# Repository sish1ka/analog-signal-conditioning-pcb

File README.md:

# Analog Signal-Conditioning PCB

## Overview

This project involves the design of a small analog signal-conditioning circuit intended to convert a 0–1 V sensor signal into a 0–3 V output suitable for microcontroller ADC interfacing.

The circuit was designed and simulated using LTspice and implemented
as a 2-layer PCB using KiCad.

## Objectives

- Design an analog amplification stage
- Implement low-pass filtering
- Maintain an ADC-compatible 0–3 V output
- Verify circuit behavior through simulation
- Design and verify a 2-layer PCB

## Tools

- LTspice
- KiCad

## Circuit Design

## Design Summary

| Parameter | Value |
|---|---:|
| Input signal | 0–1 V |
| Output signal | 0–3 V |
| Supply | +5 V |
| Amplifier | LM358 non-inverting |
| Voltage gain | 3× |
| Low-pass filter | 1st-order RC |
| Filter cutoff | ~1.59 kHz |
| PCB layers | 2 |
| PCB dimensions | 60 × 40 mm |

## LTspice Simulation

### Frequency Response

### Transient Response

### Verification Procedure

The circuit was verified using a node-by-node transient analysis.
Each verification step checks a specific electrical condition before
proceeding to the next stage.

### 1. Op-Amp Supply Voltage Verification

**Purpose:**  
Verify that the op-amp is receiving the required +5 V supply voltage before evaluating signal behavior.

**Procedure:**

1. Run a transient analysis in LTspice.
2. Probe the op-amp positive supply node (`V+`).
3. Confirm that the supply voltage is approximately +5 V.
4. Verify that the supply voltage remains stable throughout the simulation.

**Expected Result:**

| Parameter | Expected |
|---|---:|
| Supply voltage (`V+`) | +5 V |
| Supply stability | Stable |

**Measured Result:**  
`V+ = 5.00 V`

**Result:** Pass

### 2. Voltage Gain Verification

**Purpose:**  
Verify that the measured voltage gain agrees with the theoretical gain determined by the feedback resistors.

**Theoretical Gain:**

$$
A_v = 1 + \frac{R_2}{R_1}
$$

$$
A_v = 1 + \frac{20k\Omega}{10k\Omega} = 3
$$

**Procedure:**
1. Measure the input signal amplitude from the transient analysis.
2. Measure the output signal amplitude.
3. Calculate the measured voltage gain using:

$$
A_v = \frac{V_{out}}{V_{in}}
$$

4. Compare the measured gain with the theoretical gain of 3×.

**Expected Result:**

| Parameter | Expected |
|---|---:|
| Theoretical gain | 3× |
| Measured gain | ~3× |
| Gain error | Minimal |

**Measured Result:**  
`Theoretical gain = 3.00×`  
`Measured gain = Vout / Vin = 3.00×`

**Result:** Pass

### 3. Input and Op-Amp Output Verification

**Purpose:**  
Verify that the input signal has the expected amplitude and frequency, and that the op-amp produces the expected amplified output.

**Procedure:**
1. Run a transient analysis for 100 ms in LTspice.
2. Probe the input node of the op-amp.
3. Verify that the input signal is a 50 mV amplitude, 60 Hz sine wave centered around 0 V.
4. Probe the op-amp output node.
5. Verify that the output waveform follows the input waveform with the expected 3× voltage gain.
6. Compare the measured input and output amplitudes.

**Expected Result:**

| Parameter | Input | Op-Amp Output |
|---|---:|---:|
| Peak amplitude | 50 mV | ~150 mV |
| Peak-to-peak voltage | 100 mV | ~300 mV |
| Frequency | 60 Hz | 60 Hz |
| DC offset | 0 V | 0 V |
| Voltage gain | — | ~3× |

**Measured Result:**  
`Vin = 50 mV peak`  
`Vout = 150 mV peak`  
`f = 60 Hz`  
`Gain = Vout / Vin ≈ 3`

**Result:**  Pass

### 4. Filter Response Verification

**Purpose:**  
Verify the frequency response of the RC low-pass filter and confirm that the measured cutoff frequency agrees with the theoretical value.

**Filter Configuration:**

| Component | Value |
|---|---:|
| R3 | 10 kΩ |
| C1 | 10 nF |
| Filter type | Low-pass |

**Theoretical Cutoff Frequency:**

$$
f_c = \frac{1}{2\pi R_3 C_1}
$$

$$
f_c = \frac{1}{2\pi(10\,k\Omega)(10\,nF)}
$$

$$
f_c \approx 1.59\,kHz
$$

**Procedure:**
1. Set the input voltage source AC amplitude to 1 V for AC analysis.
2. Run an AC analysis using:
   `.ac dec 100 10 100k`
3. Plot the output voltage magnitude `V(VOUT)`.
4. Identify the low-frequency output magnitude.
5. Determine the frequency where the magnitude is approximately 3 dB below the low-frequency value.
6. Compare the measured cutoff frequency with the theoretical value.

**Expected Result:**

| Parameter | Expected |
|---|---:|
| Low-frequency gain | ~9.54 dB |
| Filter type | Low-pass |
| Theoretical cutoff frequency | ~1.59 kHz |
| Magnitude at cutoff | ~6.54 dB |
| Roll-off after cutoff | ~−20 dB/decade |

The low-frequency gain is approximately 9.54 dB because the op-amp provides a voltage gain of 3×:

$$
20\log_{10}(3) \approx 9.54\ dB
$$

Therefore, the -3 dB cutoff point is approximately:

$$
9.54 - 3 = 6.54\ dB
$$

**Measured Result:**  
`Low-frequency gain ≈ 9.5 dB`  
`Measured cutoff frequency ≈ 1.6 kHz`

The measured cutoff frequency agrees closely with the theoretical value of approximately 1.59 kHz.

**Result:** Pass

### Results

| Verification | Theoretical | Measured | Error | Result |
|---|---:|---:|---:|---|
| Voltage gain | 3.00× | 3.00× | 0% | Pass |
| Low-frequency gain | 9.54 dB | 9.5 dB | 0.42% | Pass |
| Filter cutoff | 1.59 kHz | 1.60 kHz | 0.63% | Pass |
| PCB DRC errors | 0 | 0 | — | Pass |

## PCB Design

### Components

| Reference | Component | Value | Footprint |
|---|---|---|---|
| U1 | LM358 Dual Op-Amp | LM358 | `Package_SO:SOIC-8_3.9x4.9mm_P1.27mm` |
| R1 | Resistor | 10 kΩ | `Resistor_SMD:R_0805_2012Metric_Pad1.18x1.45mm_HandSolder` |
| R2 | Resistor | 20 kΩ | `Resistor_SMD:R_0805_2012Metric_Pad1.18x1.45mm_HandSolder` |
| R3 | Resistor | 10 kΩ | `Resistor_SMD:R_0805_2012Metric_Pad1.18x1.45mm_HandSolder` |
| C1 | Ceramic Capacitor | 10 nF | `Capacitor_SMD:C_0805_2012Metric_Pad1.18x1.45mm_HandSolder` |
| C2 | Ceramic Capacitor | 100 nF | `Capacitor_SMD:C_0805_2012Metric_Pad1.18x1.45mm_HandSolder` |
| J1 | 2-Pin Terminal Block | Input | `TerminalBlock_Altech:Altech_AK100_1x02_P5.00mm` |
| J2 | 2-Pin Terminal Block | Output | `TerminalBlock_Altech:Altech_AK100_1x02_P5.00mm` |
| J3 | 2-Pin Terminal Block | Power | `TerminalBlock_Altech:Altech_AK100_1x02_P5.00mm` |

### Connector Pinout

| Connector | Pin 1 | Pin 2 |
|---|---|---|
| J1 – Input | VIN | GND |
| J2 – Output | VOUT | GND |
| J3 – Power | +5 V | GND |

### Circuit Parameters

| Parameter | Value |
|---|---:|
| Supply Voltage | +5 V |
| Input Range | 0–1 V |
| Voltage Gain | 3× |
| Output Range | 0–3 V |
| Filter | RC Low-Pass |
| Cutoff Frequency | ~1.59 kHz |

### KiCAD schematic 

### PCB Layout

### 3D View

### Fabrication Outputs

Gerber and drill files were generated using KiCad for PCB manufacturing.

The fabrication outputs include:
- Front and back copper
- Front and back solder mask
- Silkscreen
- Board outline
- Drill files

The generated files are available in `KiCad/Gerbers/`.

### PCB Design Verification

The PCB layout was checked using KiCad's Design Rules Checker (DRC).

**Result:**
- DRC errors: 0
- Unconnected items: 0
- Board outline: 60 × 40 mm

The design passed the final DRC check before fabrication outputs were generated.

## Files

- `Documentation/` — design images and results
- `KiCad/` — schematic and PCB design files
- `LTspice/` — circuit simulations
- `BOM/` — bill of materials
- `Gerbers/` — manufacturing outputs

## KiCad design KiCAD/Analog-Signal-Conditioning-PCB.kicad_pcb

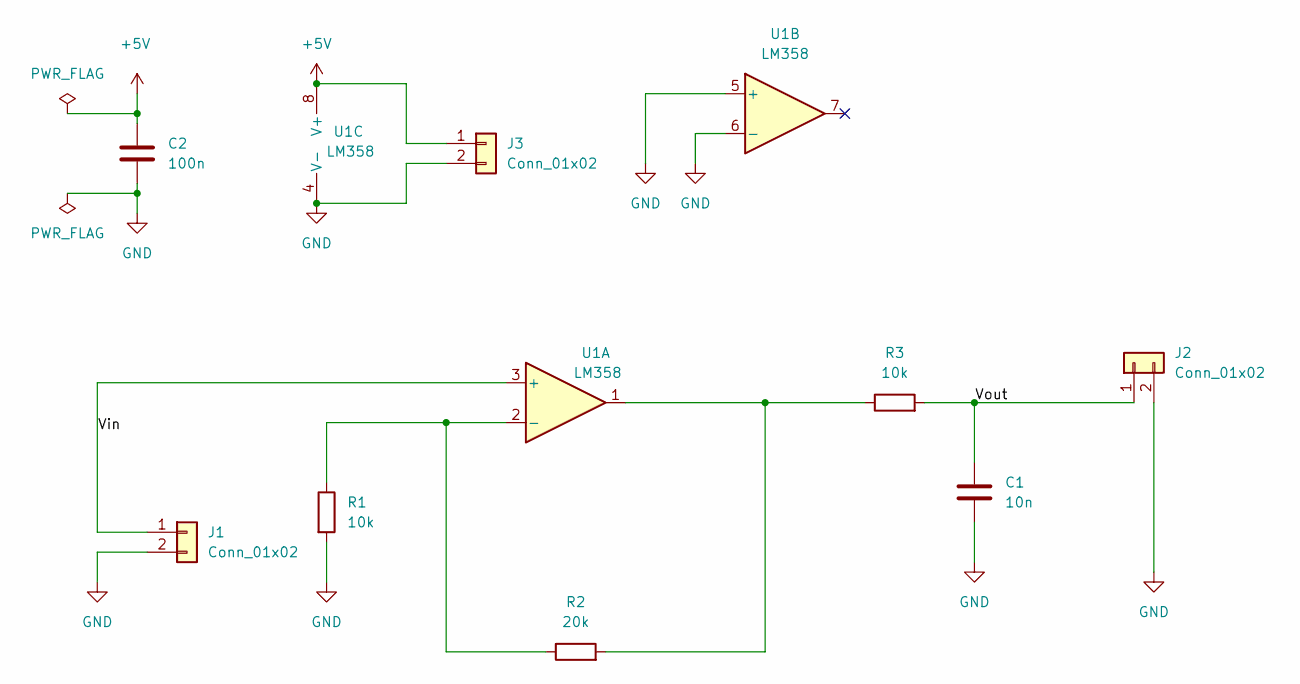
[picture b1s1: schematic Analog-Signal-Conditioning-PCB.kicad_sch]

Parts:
C1: 10n; C_0805_2012Metric_Pad1.18x1.45mm_HandSolder
C2: 100n; C_0805_2012Metric_Pad1.18x1.45mm_HandSolder
J1, J2, J3: Conn_01x02; Altech_AK100_1x02_P5.00mm
R1, R3: 10k; R_0805_2012Metric_Pad1.20x1.40mm_HandSolder
R2: 20k; R_0805_2012Metric_Pad1.20x1.40mm_HandSolder
U1: LM358; SOIC-8_3.9x4.9mm_P1.27mm

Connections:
+5V: C2.1, J3.1, U1.8 (V+)
/Vin: J1.1, U1.3 (+)
/Vout: C1.1, J2.1, R3.2
GND: C1.2, C2.2, J1.2, J2.2, J3.2, R1.2, U1.4 (V-), U1.5 (+), U1.6 (-)
unnamed: R2.2, R3.1, U1.1
unnamed: R1.1, R2.1, U1.2 (-)

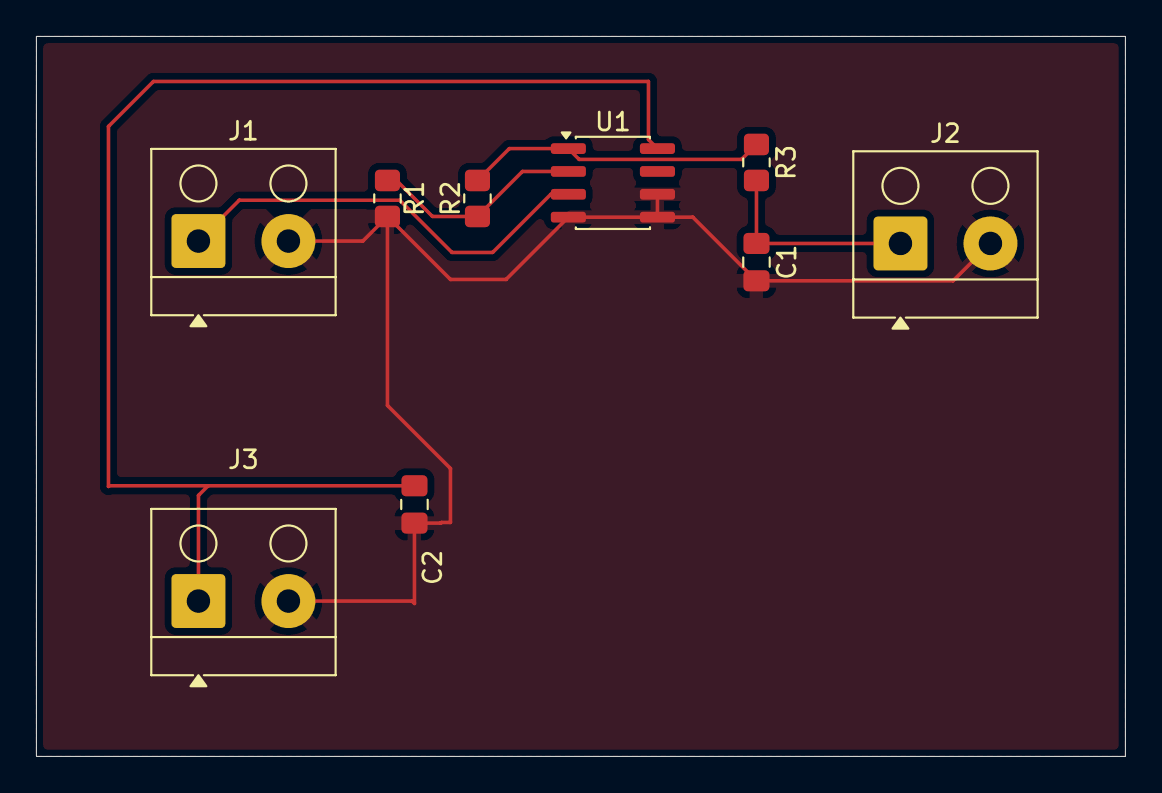
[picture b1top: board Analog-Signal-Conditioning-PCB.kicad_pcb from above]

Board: 2 copper layers, 60.5 x 40.0 mm, 9 parts (0 on the bottom side), 6 nets.

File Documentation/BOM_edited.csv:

| Ref    | Component            |  Value | Qty |
| ------ | -------------------- | -----: | --: |
| C1     | Ceramic capacitor    |  10 nF |   1 |
| C2     | Ceramic capacitor    | 100 nF |   1 |
| J1–J3  | 2-pin terminal block |      — |   3 |
| R1, R3 | Resistor             |  10 kΩ |   2 |
| R2     | Resistor             |  20 kΩ |   1 |
| U1     | LM358 dual op-amp    |  LM358 |   1 |
